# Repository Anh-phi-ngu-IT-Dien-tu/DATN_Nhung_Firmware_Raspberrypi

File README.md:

https://youtu.be/jIvI4DPsrL0?si=QmMiYuXoHqMDy0yn

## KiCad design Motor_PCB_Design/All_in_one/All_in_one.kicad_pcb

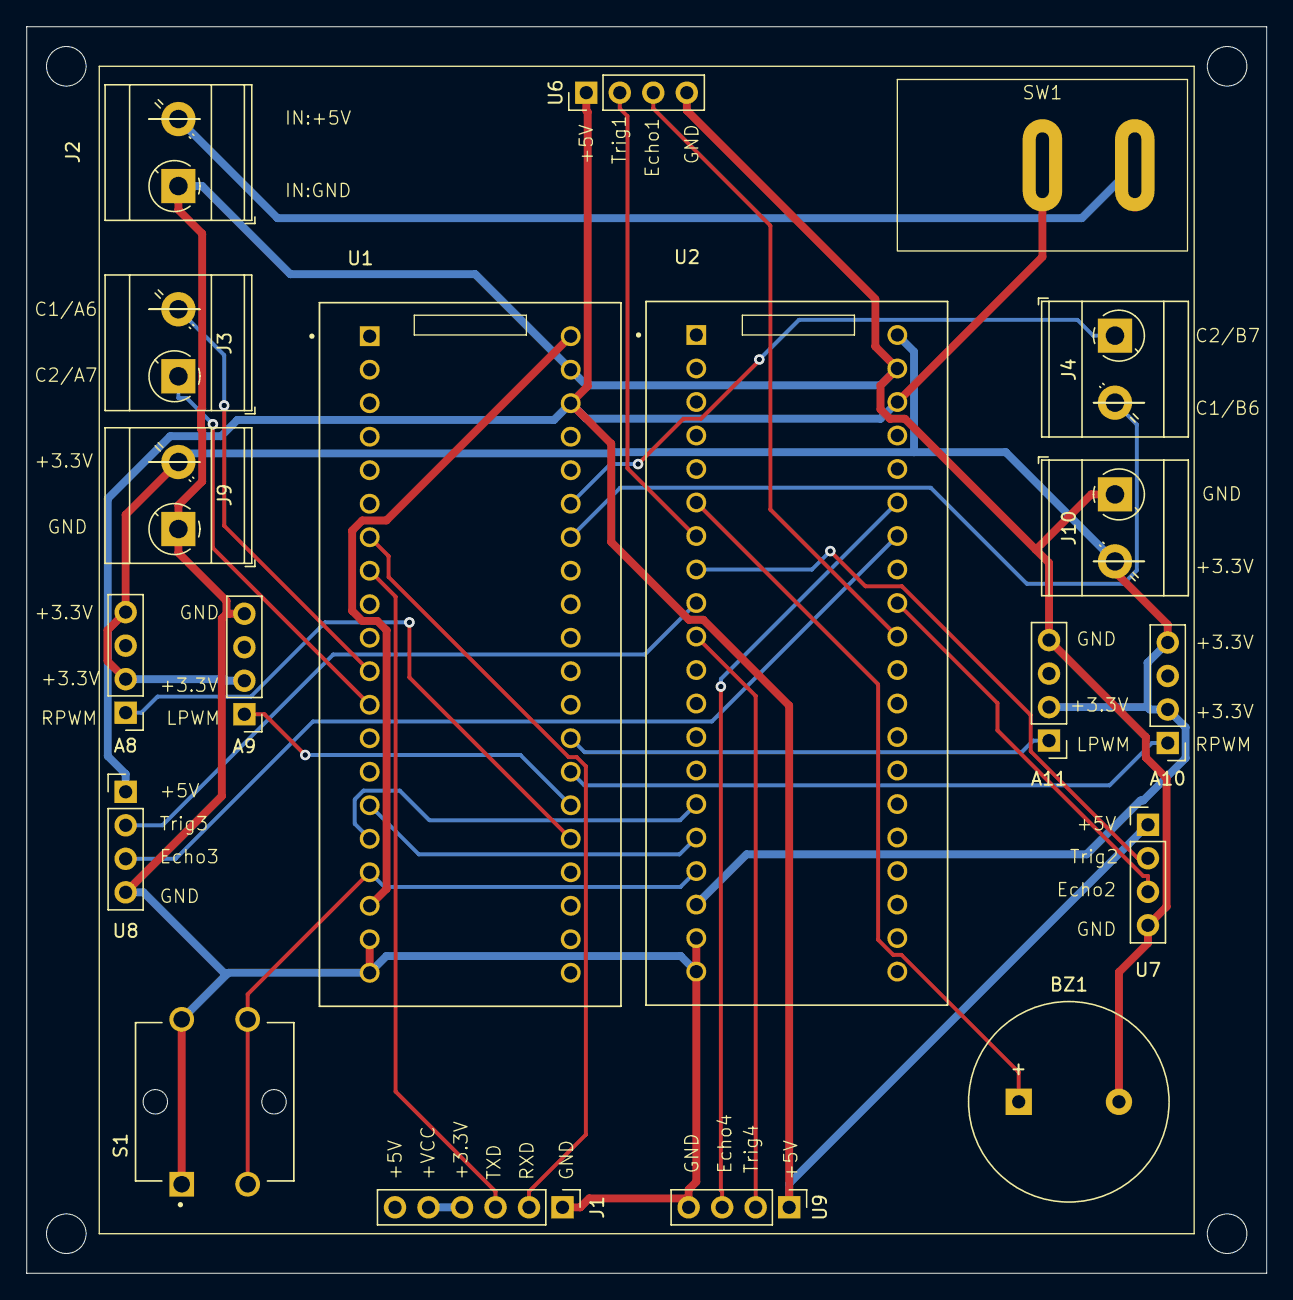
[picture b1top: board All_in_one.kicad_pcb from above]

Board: 2 copper layers, 94.0 x 94.5 mm, 19 parts (0 on the bottom side), 28 nets.

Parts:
A8, A9, A10, A11: Conn_01x04_Pin; PinHeader_1x04_P2.54mm_Vertical
BZ1: Buzzer; Buzzer_15x7.5RM7.6
J1: Conn_01x06_Pin; PinHeader_1x06_P2.54mm_Vertical
J2, J3, J4, J9, J10: Conn_01x02_Pin; TerminalBlock_MetzConnect_Type073_RT02602HBLU_1x02_P5.08mm_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
S1: B3F-4055; SW_B3F-4055
SW1: SW_DPST_x2; Switch_6A_21x22x15custom
U1, U2: ZC323000; MODULE_ZC323000
U6, U7, U8, U9: PinHeader_1x04_P2.54mm_Vertical

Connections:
+3.3V: A8.2, A8.4, A9.2, A10.2, A10.4, A11.2, J9.2, J10.2, U2.18 (3.3), U2.40 (3.3)
+5V: SW1.1 (A), U1.38 (5V), U2.38 (5V), U6.1 (Vcc), U7.1 (Vcc), U8.1 (Vcc), U9.1 (Vcc)
+5VL: J2.2, SW1.2 (B)
/+3.3V_MCU1: U1.18 (3.3), U1.40 (3.3)
/+3.3V_USB: J1.4, J1.5
/A1_MCU2: BZ1.1 (+), U2.6 (A1)
/A2_MCU2: U2.7 (A2), U6.2 (Trig)
/A2_TX2_MCU1: J1.2, U1.7 (A2)
/A3_MUC2: U2.8 (A3), U7.2 (Trig)
/A3_RX2_MCU1: J1.3, U1.8 (A3)
/A4_MCU2: U2.9 (A4), U8.2 (Trig)
/A5_MCU2: U2.10 (A5), U9.2 (Trig)
/A6_MCU1: J3.2, U1.11 (A6)
/A7_MCU1: J3.1, U1.12 (A7)
/A8_MCU1: A8.1, U1.25 (A8)
/A9_MCU1: A9.1, U1.26 (A9)
/A10_MCU1: A10.1, U1.27 (A10)
/A11_MCU1: A11.1, U1.28 (A11)
/B3_MCU2: U2.31 (B3), U6.3 (Echo)
/B4_MCU2: U2.32 (B4), U7.3 (Echo)
/B6_MCU1: J4.2, U1.34 (B6)
/B6_MCU2: U2.34 (B6), U8.3 (Echo)
/B7_MCU1: J4.1, U1.35 (B7)
/B7_MCU2: U2.35 (B7), U9.3 (Echo)
/B10_TX3_MCU1: U1.15 (B10), U2.16 (B11)
/B10_TX3_MCU2: U1.16 (B11), U2.15 (B10)
/R: S1.3, S1.4, U1.17 (R), U2.17 (R)
GND: A9.4, A11.4, BZ1.2 (-), J1.1, J2.1, J9.1, J10.1, S1.1, S1.2, U1.19 (G), U1.20 (G), U1.39 (G), U2.19 (G), U2.20 (G), U2.39 (G), U6.4 (Gnd), U7.4 (Gnd), U8.4 (Gnd), U9.4 (Gnd)

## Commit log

2025-02-13 Add .gitignore file
2025-02-13 Remove unnecessary files
2025-02-16 version 1.1
2025-02-18 18/2/2025 5:30PM
2025-02-18 18/2/2025 20:19
2025-02-21 21/2/2025 3:42PM
2025-02-25 25/2/2025 4:13 PM
2025-03-04 3:00 PM 4/3/2025
2025-03-04 5:08 PM 4/3/2025
2025-03-07 2:54PM 7/3/2025
2025-03-08 8/3/2025 8:38PM
2025-03-10 10/3/202512:35PM
2025-03-16 With ultrasonic
2025-03-16 First
2025-03-18 18/3/2025
2025-03-21 21/3/2025 2:17 PM
2025-03-23 Comparison
2025-03-24 Compare object
2025-03-25 ESP32
2025-03-25 25/3/2025 1:33PM
2025-03-27 Change Comparison
2025-03-27 27/3/2025
2025-03-28 28/3/2025 7:56AM
2025-03-28 small
2025-03-28 28/3/2025 12:06PM
2025-03-28 dummy
2025-03-28 test main.py
2025-03-30 30/3/2025 11:36PM
2025-04-01 1/4/2025 1:11PM
2025-04-01 1/4/2025 3:10PM
2025-04-02 Fix Vision algorithm
2025-04-03 Add shelf 2
2025-04-04 4/4/2025 8:14PM
2025-04-07 fix-oos
2025-04-07 fix-oos2
2025-04-08 8/4/2025 10:28AM
2025-04-08 8/4/2025
2025-04-13 13/4/2025 10:49PM
2025-04-14 14/4/2025 11:50PM
2025-04-14 14/4/2025 11:51PM
2025-04-15 15/4/2025 9:33PM
2025-04-15 15/4/2025 9:34PM
2025-04-16 Debug
2025-04-16 Debug2
2025-04-16 Debug3
2025-04-16 16/4/2025 10:09PM
2025-04-17 test
2025-04-17 17/4/2025 10:41 PM
2025-04-17 add time
2025-04-17 Add delete sub shelf
2025-04-20 Add load shelf
2025-04-21 21/4/2025 9:12PM
2025-04-22 22/4/2025 10:00AM
2025-04-22 22/4/2025 4:58PM
2025-04-24 25/4/2025 12:21AM
2025-04-25 25/4/2025 8:30AM
2025-04-25 11:44AM
2025-04-26 26/4/2025 9:04PM
2025-04-27 27/4/2025 8:12AM
2025-04-27 27/4/2025 8:15AM
2025-04-28 28/4/2025 7:21PM
2025-04-29 29/4/2025 8:17AM
2025-04-29 New model
2025-04-29 File
2025-04-29 29/4/2025 4:06PM
2025-04-29 Return
2025-05-01 data
2025-06-12 Circuit
2025-06-22 readme
2025-06-24 chore: update
2025-06-24 chore: add folders from other branch into main
2025-06-24 chore: Update readme.md
2025-06-24 chore: add usage
